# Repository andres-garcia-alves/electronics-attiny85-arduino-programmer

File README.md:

# ATtiny85 Arduino Programmer

Electronic proyect to turn an Arduino Nano/UNO into an ATtiny85 programmer.  

Based on video [CREA tu Programador DIY para ATTINY85 con Arduino UNO](https://www.youtube.com/watch?v=IFw5A_K7DOM) (spanish) from [Kriss Electronics](https://www.youtube.com/@KrissElectronics) YouTube channel.

&nbsp;

This project use the following electronic components:
- 1 x Arduino Nano v3.0 (or Arduino UNO)
- 1 x Atmel ATtiny85
- 1 x Capacitor 10uF/16V
- 2 x 1-pin header
- 2 x 2-pins header
- 1 x 3-pins header

Notes:
- PCB pin-headers 5V-GND-RST-10-11-12-13 allows to program the ATtiny85 from an Arduino UNO, instead of Arduino Nano.
- Remove from PCB any pluged Arduino Nano if you are going to program the ATtiny85 from Arduino UNO pin-headers.
- Please refer to above video, to learn about requiered Arduino IDE configuration and programming process.

&nbsp;

### Screenshots

| Breadboard                                         | PCB Manufacturing                                  |
|----------------------------------------------------|----------------------------------------------------|
|                 |          |

| PCB Assembly                                       | PCB Assembly                                       |
|----------------------------------------------------|----------------------------------------------------|
|               |               |

| Schematics Diagram                                 | PCB Layout                                         |
|----------------------------------------------------|----------------------------------------------------|
|             |                    |

| PCB 3D Render                                      | PCB 3D Render                                      |
|----------------------------------------------------|----------------------------------------------------|
|              |             |

| Case 3D Model                                      | Project Final                                      |
|----------------------------------------------------|----------------------------------------------------|
|                 |                 |

See 'Rescources' sub-folder for more pictures & videos of the project.

&nbsp;

### Version History

v1.0 (2023.05.26) - Initial release.  
v1.1 (2023.05.29) - Optimizing PCB size.  
v1.2 (2023.05.31) - Fixed PCB bug.  
v1.3 (2025.12.30) - Update project structure.  
v1.4 (2026.01.12) - Minor PCB improvements.  
v1.5 (2026.01.16) - Adding case 3D model.  

&nbsp;

This source code is licensed under GPL v3.0  
Please send me your feedback about this project: andres.garcia.alves@gmail.com

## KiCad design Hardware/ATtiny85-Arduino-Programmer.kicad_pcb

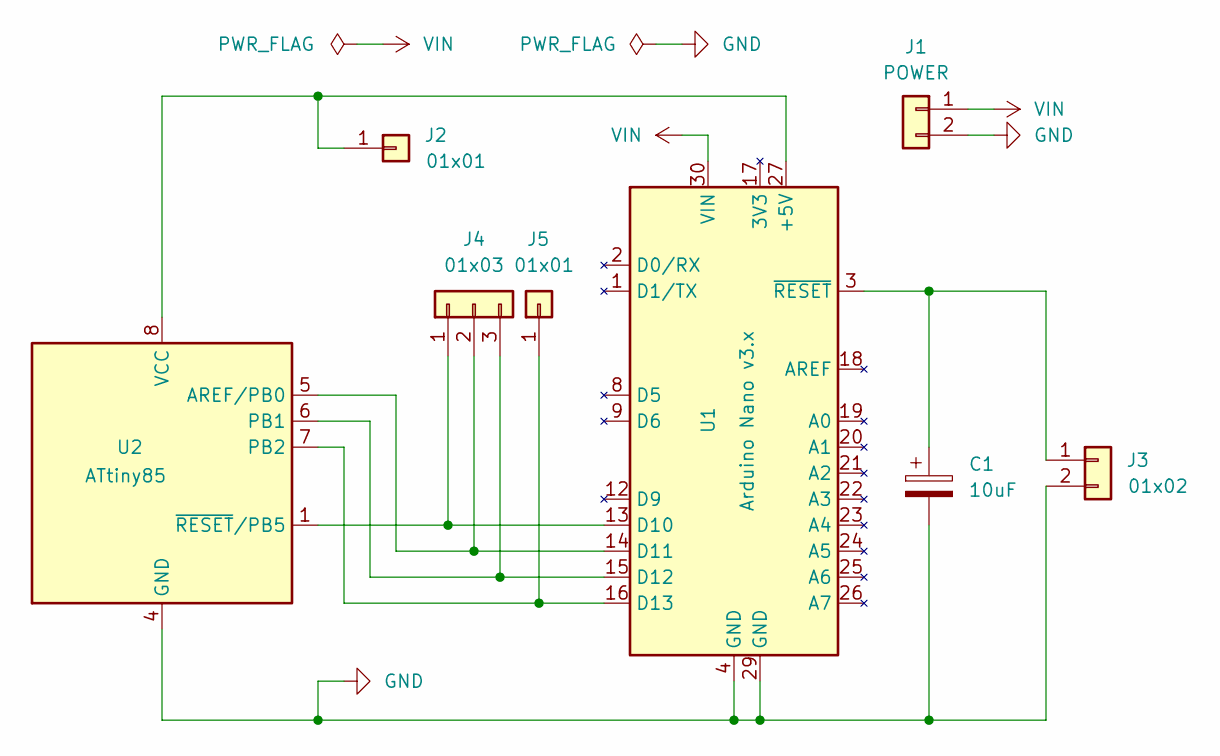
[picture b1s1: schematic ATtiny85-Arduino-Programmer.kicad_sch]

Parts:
C1: 10uF; CP_Radial_D5.0mm_P2.50mm
J1: POWER; PinHeader_1x02_P2.54mm_Vertical
J2, J5: 01x01; PinHeader_1x01_P2.54mm_Vertical
J3: 01x02; PinHeader_1x02_P2.54mm_Vertical
J4: 01x03; PinHeader_1x03_P2.54mm_Vertical
U1: Arduino Nano v3.x; Arduino_Nano_v3
U2: ATtiny85; DIP-8_W7.62mm

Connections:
GND: C1.2, J1.2, J3.2, U1.4 (GND), U1.29 (GND), U2.4 (GND)
unnamed: J2.1, U1.27 (+5V), U2.8 (VCC)
unnamed: C1.1, J3.1, U1.3 (~RESET)
unnamed: J4.1, U1.13 (D10), U2.1 (~RESET/PB5)
unnamed: J4.2, U1.14 (D11), U2.5 (AREF/PB0)
unnamed: J4.3, U1.15 (D12), U2.6 (PB1)
unnamed: J5.1, U1.16 (D13), U2.7 (PB2)
VIN: J1.1, U1.30 (VIN)

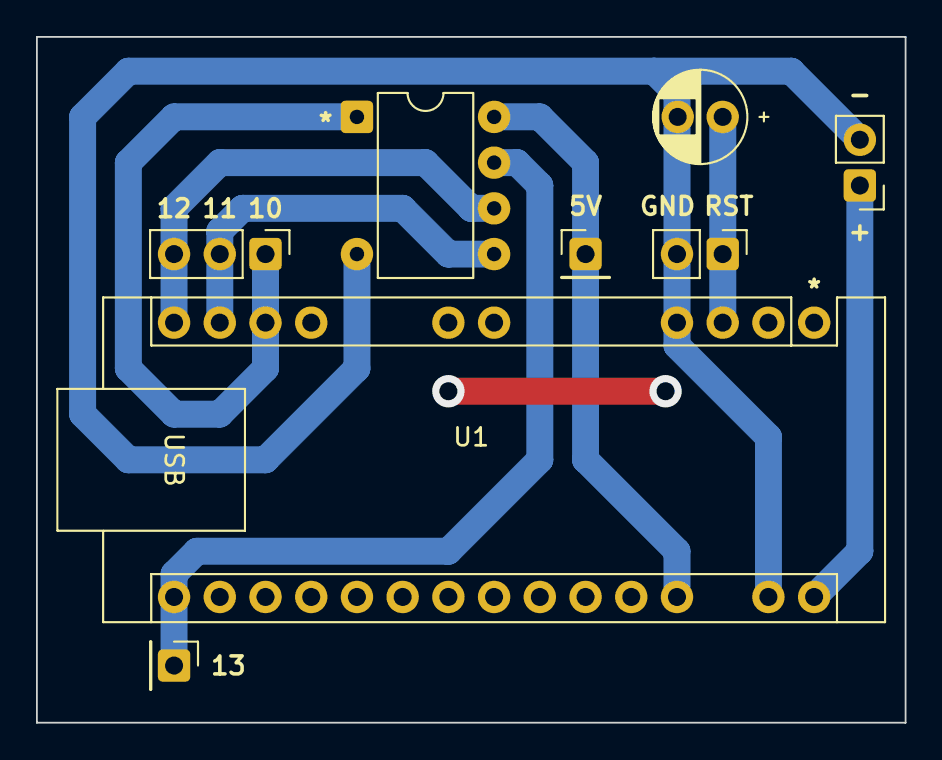
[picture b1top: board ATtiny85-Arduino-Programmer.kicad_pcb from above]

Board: 2 copper layers, 48.3 x 38.1 mm, 8 parts (0 on the bottom side), 8 nets.

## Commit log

2025-12-20 update project structure
2026-01-12 Minor PCB improvements
2026-01-16 Adding case 3D model
2026-02-02 Update Tracks
